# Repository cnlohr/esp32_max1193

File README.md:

# esp32_max1193
Let's just see what happens when you slap em together?

I built the boards, but haven't had any time to test them yet - Nov 6, 2018

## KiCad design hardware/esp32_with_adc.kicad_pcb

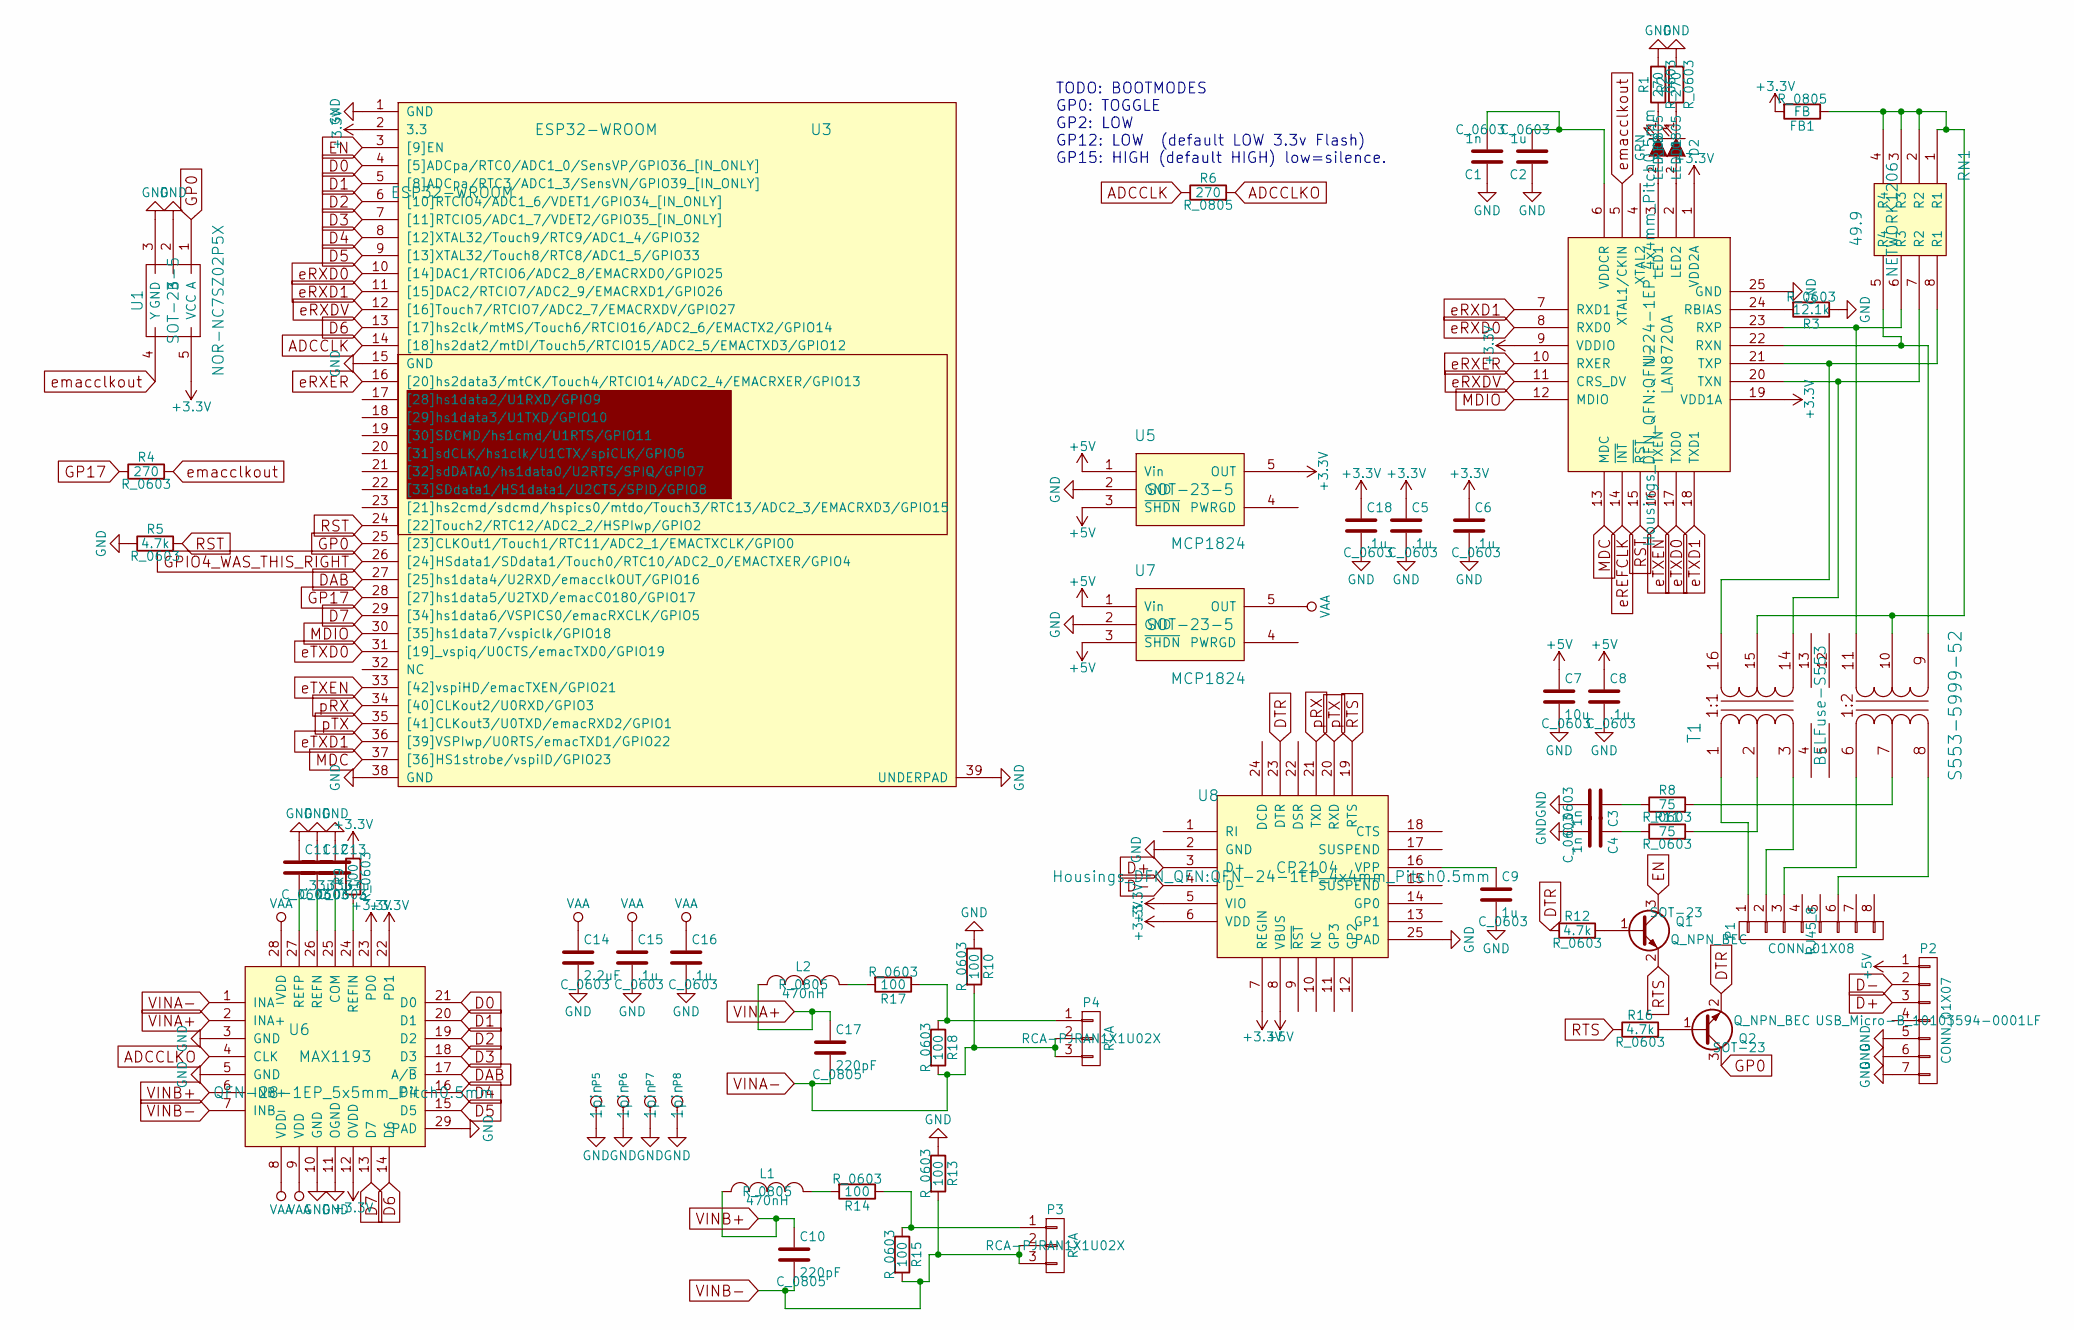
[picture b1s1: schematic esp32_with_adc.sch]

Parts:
C1, C3, C4: 1n; C_0603
C2, C9: 1u; C_0603
C5, C6, C8, C15, C16, C18: .1u; C_0603
C7: 10u; C_0603
C10, C17: 220pF; C_0805
C11, C12, C13: .33u; C_0603
C14: 2.2uF; C_0603
D1: GRN; LED_0805
D2: RED; LED_0805
FB1: FB; R_0805
L1, L2: 470nH; R_0805
P1: CONN_01X08; RJ45_8
P2: CONN_01X07; USB_Micro-B_10103594-0001LF
P3, P4: RCA; RCA-PJRAN1X1U02X
P5, P6, P7, P8: 1pin
Q1, Q2: Q_NPN_BEC; SOT-23
R1, R2, R4: 270; R_0603
R3: 12.1k; R_0603
R5, R12, R16: 4.7k; R_0603
R6: 270; R_0805
R8, R11: 75; R_0603
R9, R10, R13, R14, R15, R17, R18: 100; R_0603
RN1: 49.9; NETWORK1206
T1: S553-5999-52; BELFuse-S553
U1: NOR-NC7SZ02P5X; SOT-23-5
U2: LAN8720A; QFN-24-1EP_4x4mm_Pitch0.5mm
U3: ESP32-WROOM
U5, U7: MCP1824; SOT-23-5
U6: MAX1193; QFN-28-1EP_5x5mm_Pitch0.5mm
U8: CP2104; QFN-24-1EP_4x4mm_Pitch0.5mm

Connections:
+3V3: C5.1, C6.1, C18.1, FB1.2, R9.2, U1.5 (VCC), U2.1 (VDD2A), U2.9 (VDDIO), U2.19 (VDD1A), U3.2 (3.3), U5.5 (OUT), U6.12 (OVDD), U6.22 (PD1), U6.23 (PD0), U8.5 (VIO), U8.6 (VDD), U8.7 (REGIN)
+5V: C7.1, C8.1, P2.1, U5.1 (Vin), U5.3 (~SHDN), U7.1 (Vin), U7.3 (~SHDN), U8.8 (VBUS)
ADCCLK: R6.1, U3.14 ([18]hs2dat2/mtDI/Touch5/RTCIO15/ADC2_5/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)
ADCCLKO: R6.2, U6.4 (CLK)
D0: U3.4 ([5]ADCpa/RTC0/ADC1_0/SensVP/GPIO36_[IN_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), U6.21 (D0)
D1: U3.5 ([8]ADCpa/RTC3/ADC1_3/SensVN/GPIO39_[IN_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), U6.20 (D1)
D2: U3.6 ([10]RTCIO4/ADC1_6/VDET1/GPIO34_[IN_ONLY]), U6.19 (D2)
D3: U3.7 ([11]RTCIO5/ADC1_7/VDET2/GPIO35_[IN_ONLY]), U6.18 (D3)
D4: U3.8 ([12]XTAL32/Touch9/RTC9/ADC1_4/GPIO32), U6.16 (D4)
D5: U3.9 ([13]XTAL32/Touch8/RTC8/ADC1_5/GPIO33), U6.15 (D5)
D6: U3.13 ([17]hs2clk/mtMS/Touch6/RTCIO16/ADC2_6/E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), U6.14 (D6)
D7: U3.29 ([34]hs1data6/VSPICS0/emacRXCLK/GPIO5), U6.13 (D7)
D+: P2.3, U8.3 (D+)
D-: P2.2, U8.4 (D-)
DAB: U3.27 ([25]hs1data4/U2RXD/emacclkOUT/GPIO16), U6.17 (A/~B~)
DTR: Q2.2 (E), R12.1, U8.23 (DTR)
EN: Q1.3 (C), U3.3 ([9]EN)
GND: C1.1, C2.1, C3.2, C4.2, C5.2, C6.2, C7.2, C8.2, C9.2, C11.1, C12.1, C13.1, C14.2, C15.2, C16.2, C18.2, P2.5, P2.6, P2.7, P5.1, P6.1, P7.1, P8.1, R1.2, R2.2, R3.1, R5.1, R10.1, R13.1, U1.2 (B), U1.3 (GND), U2.25 (GND), U3.1 (GND), U3.15 (GND), U3.38 (GND), U3.39 (UNDERPAD), U5.2 (GND), U6.3 (GND), U6.5 (GND), U6.10 (GND), U6.11 (OGND), U6.29 (PAD), U7.2 (GND), U8.2 (GND), U8.25 (PAD)
GP0: Q2.3 (C), U1.1 (A), U3.25 ([23]CLKOut1/Touch1/RTC11/ADC2_1/EMACTXC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)
GP17: R4.1, U3.28 ([27]hs1data5/U2TXD/emacC0180/GPIO17)
MDC: U2.13 (MDC), U3.37 ([36]HS1strobe/vspiID/GPIO23)
MDIO: U2.12 (MDIO), U3.30 ([35]hs1data7/vspiclk/GPIO18)
unnamed: C1.2, C2.2, U2.6 (VDDCR)
unnamed: C3.1, R8.1
unnamed: C4.1, R11.1
unnamed: C9.1, U8.16 (VPP)
unnamed: C11.2, U6.27 (REFP)
unnamed: C12.2, U6.26 (REFN)
unnamed: C13.2, U6.25 (COM)
unnamed: D1.1 (K), R1.1
unnamed: D1.2 (A), U2.3 (LED1)
unnamed: D2.1 (K), R2.1
unnamed: D2.2 (A), U2.2 (LED2)
unnamed: FB1.1, RN1.1 (R1), RN1.2 (R2), RN1.3 (R3), RN1.4 (R4), T1.10 (4), T1.15
unnamed: L1.2, R14.2
unnamed: L2.2, R17.2
unnamed: P1.1, T1.1 (RX1)
unnamed: P1.2, T1.3 (PR2)
unnamed: P1.3, T1.6 (PR1)
unnamed: P1.6, T1.8 (PR2)
unnamed: P3.1, R14.1, R15.1
unnamed: P4.1, R17.1, R18.1
unnamed: Q1.1 (B), R12.2
unnamed: Q2.1 (B), R16.2
unnamed: R3.2, U2.24 (RBIAS)
unnamed: R8.2, T1.7 (PM)
unnamed: R9.1, U6.24 (REFIN)
unnamed: R11.2, T1.2 (PM)
unnamed: RN1.5 (R4), T1.9 (S1), U2.22 (RXN)
unnamed: RN1.6 (R3), T1.11 (S2), U2.23 (RXP)
unnamed: RN1.7 (R2), T1.14 (S1), U2.20 (TXN)
unnamed: RN1.8 (R1), T1.16 (S2), U2.21 (TXP)
RST: R5.2, U2.15 (~RST~), U3.24 ([22]Touch2/RTC12/ADC2_2/HSPIwp/GPIO2)
RTS: Q1.2 (E), R16.1, U8.19 (RTS)
VAA: C14.1, C15.1, C16.1, U6.8 (VDD), U6.9 (VDD), U6.28 (VDD), U7.5 (OUT)
VINA+: C17.1, L2.1, U6.2 (INA+)
VINA-: C17.2, P4.2, P4.3, R10.2, R18.2, U6.1 (INA-)
VINB+: C10.1, L1.1, U6.6 (INB+)
VINB-: C10.2, P3.2, P3.3, R13.2, R15.2, U6.7 (INB-)
eRXD0: U2.8 (RXD0), U3.10 ([14]DAC1/RTCIO6/ADC2_8/EMACRXD0/GPIO25)
eRXD1: U2.7 (RXD1), U3.11 ([15]DAC2/RTCIO7/ADC2_9/EMACRXD1/GPIO26)
eRXDV: U2.11 (CRS_DV), U3.12 ([16]Touch7/RTCIO7/ADC2_7/EMACRXDV/GPIO27)
eRXER: U2.10 (RXER), U3.16 ([20]hs2data3/mtCK/Touch4/RTCIO14/ADC2_4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)
eTXD0: U2.17 (TXD0), U3.31 ([19]_vspiq/U0CTS/emacTXD0/GPIO19)
eTXD1: U2.18 (TXD1), U3.36 ([39]VSPIwp/U0RTS/emacTXD1/GPIO22)
eTXEN: U2.16 (TXEN), U3.33 ([42]vspiHD/emacTXEN/GPIO21)
emacclkout: R4.2, U1.4 (Y), U2.5 (XTAL1/CKIN)
pRX: U3.34 ([40]CLKout2/U0RXD/GPIO3), U8.21 (TXD)
pTX: U3.35 ([41]CLKout3/U0TXD/emacRXD2/GPIO1), U8.20 (RXD)

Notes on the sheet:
TODO: BOOTMODES GP0: TOGGLE GP2: LOW GP12: LOW (default LOW 3.3v Flash) GP15: HIGH (default HIGH) low=silence.

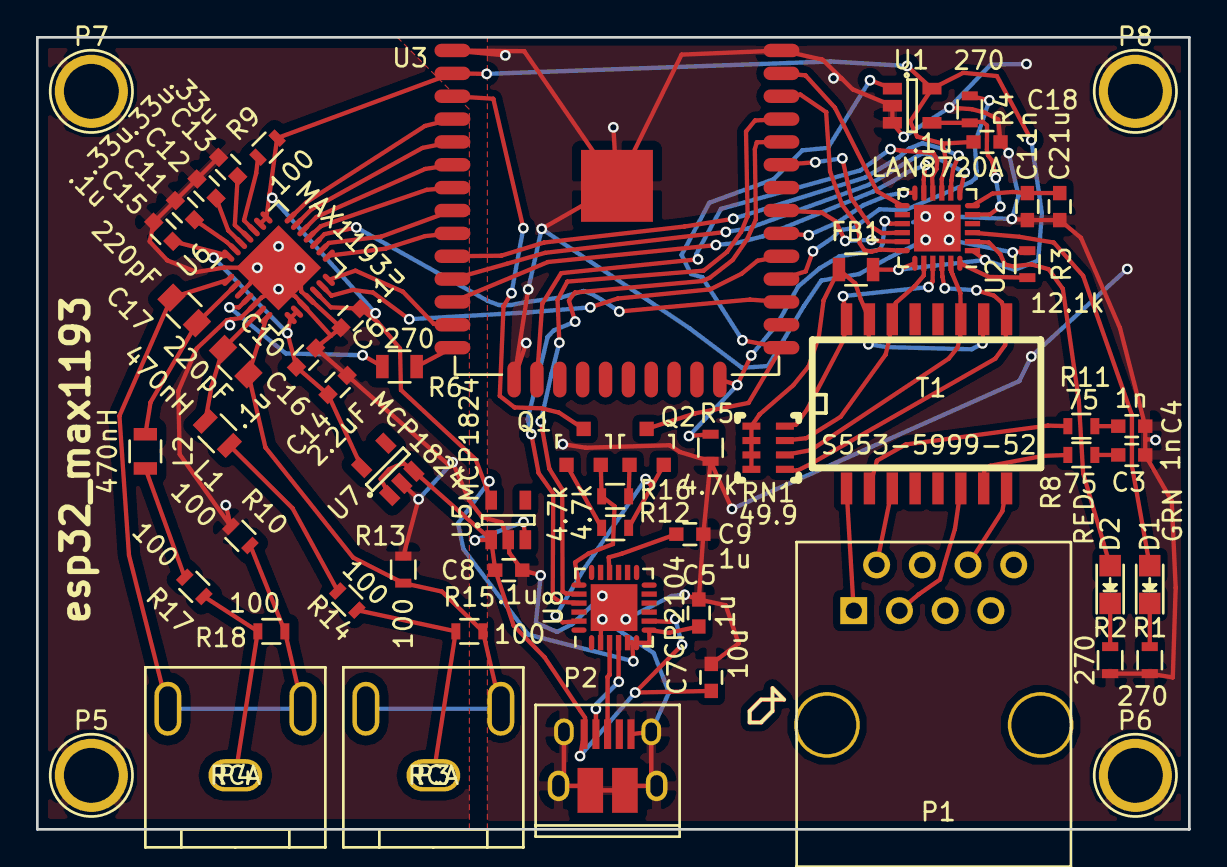
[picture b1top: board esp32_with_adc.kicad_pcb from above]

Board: 2 copper layers, 64.0 x 44.0 mm, 59 parts (0 on the bottom side), 69 nets.

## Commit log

2018-10-02 bump hardware
2018-11-02 bump notes
